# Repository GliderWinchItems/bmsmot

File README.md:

# bmsmot
This board is the control for the BMS (battery monitoring system) for one string of batteries; the contactor function, thermistor inputs for motor coolant, and output drive for enables, relays, and external high current FET sub-boards. A STM32F446RET6 is the main processor on this board.

The contactor function measures the high voltage using a STM32L431RCT6, ground isolated and communicates readings to the main processor via uart with opto-isolator. It also measures battery string current using an external Hall-effect sensor.

The main board provides for the CAN bus cabling to the BMS modules to loop back and apply +12v current to both ends of the CAN cabling, as well as in & out connectors for other nodes on the CAN bus. Provision is for a second CAN bus.

The software provides the EMC (Energy Management Control) and MMC (Motor Management Control) functions for one battery/motor installation.

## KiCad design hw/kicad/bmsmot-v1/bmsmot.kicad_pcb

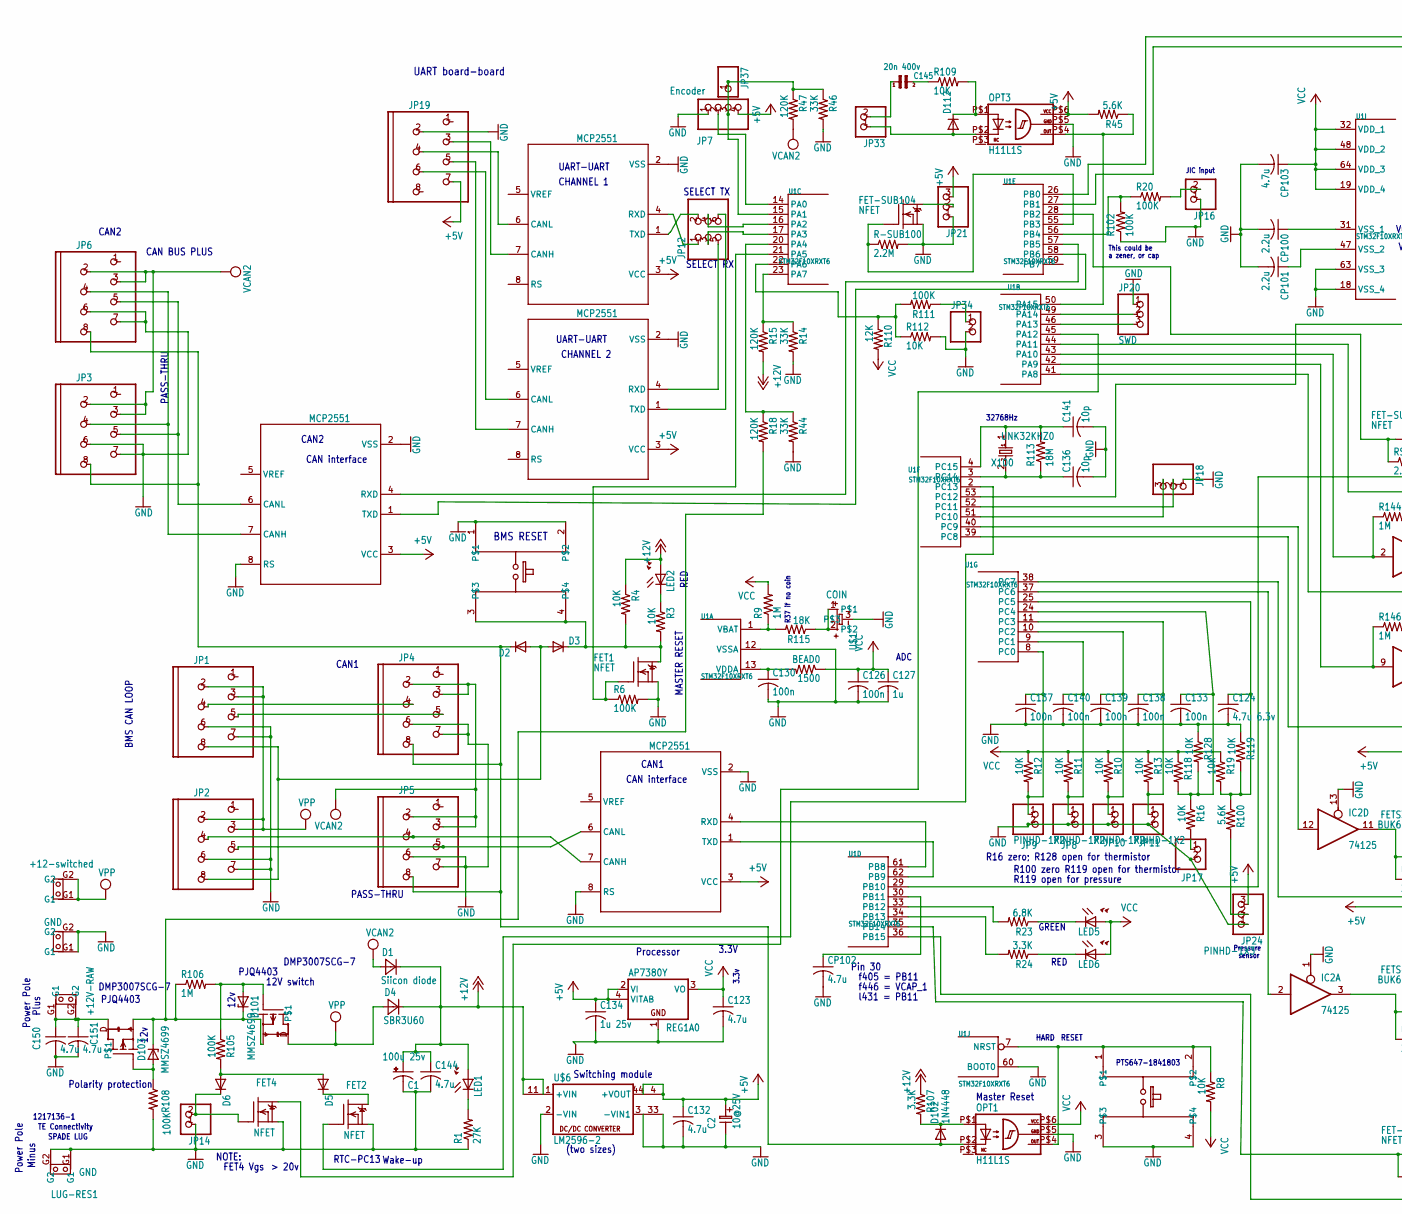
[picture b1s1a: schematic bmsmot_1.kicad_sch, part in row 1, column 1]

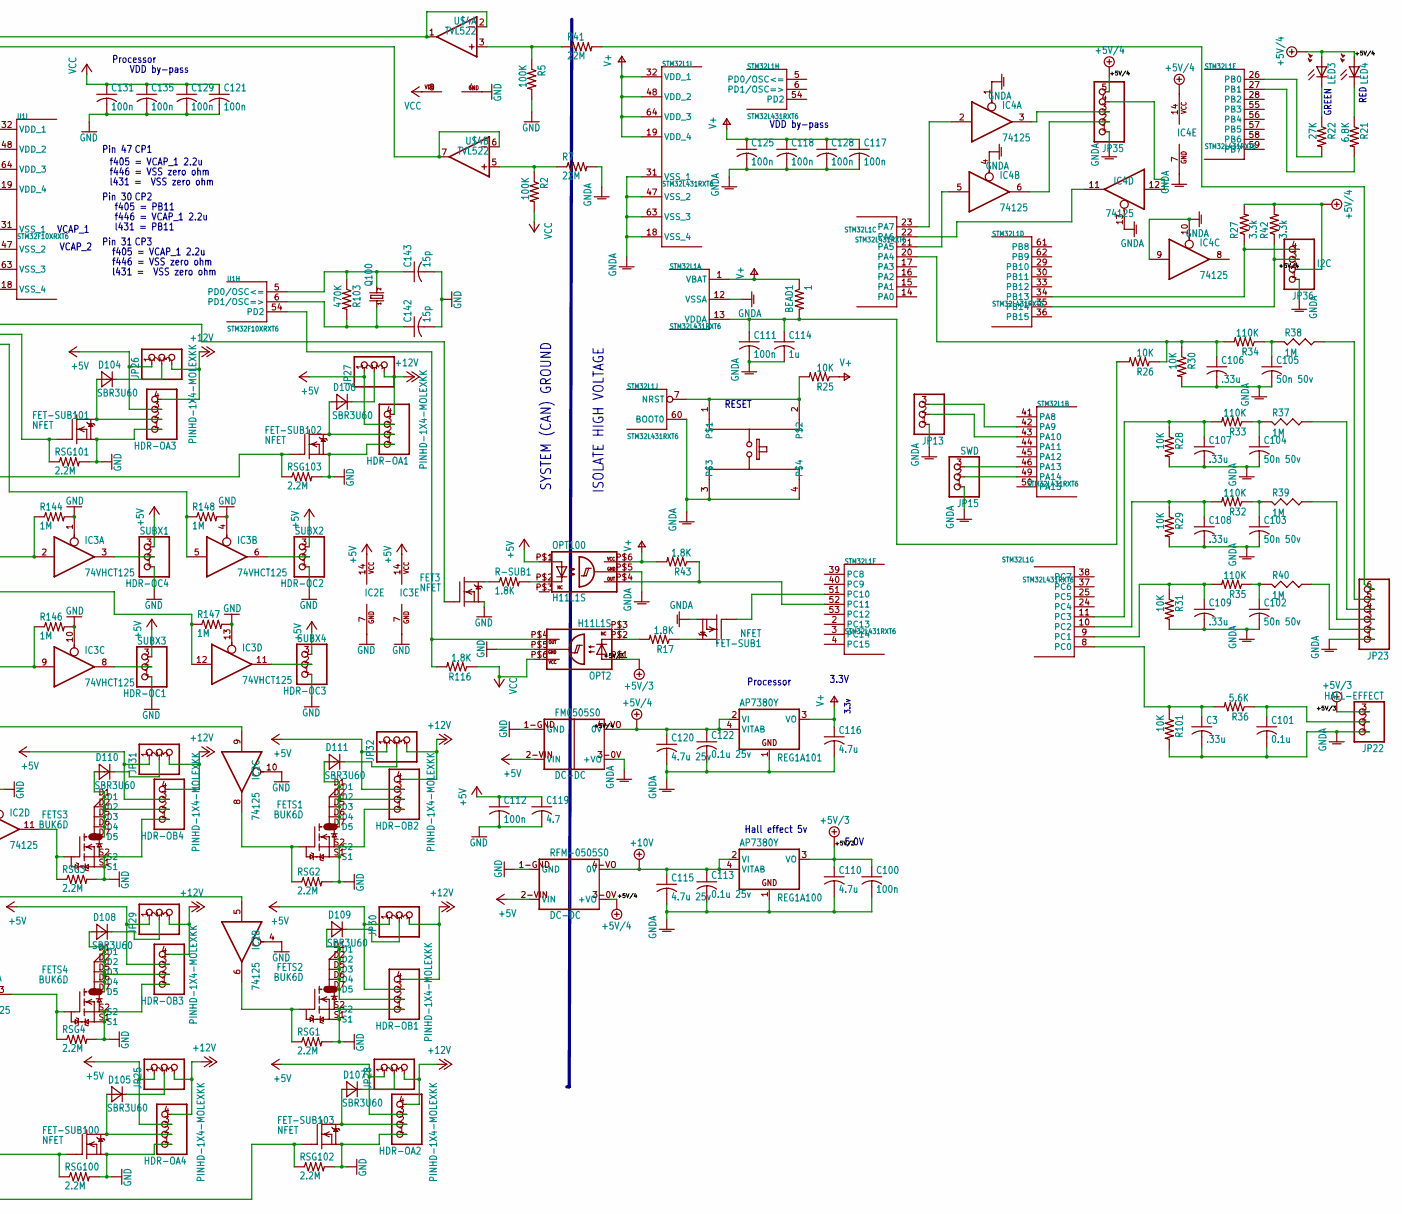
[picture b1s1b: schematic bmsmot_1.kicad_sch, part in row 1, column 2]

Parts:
+12SW0: +12-switched; SPADE_TAB
BEAD0: 1500; R0603
BEAD1: 1; R0603
BMS-RESET0: E-SWITCH2
C1: 100u 25v; E5-8,5
C2: 10@25V; ES-2,5L
C3, C106, C107, C108, C109: .33u; C0603
C100, C111, C112, C117, C118, C121, C125, C126, C128, C129, C130, C131, C133, C135, C137, C138, C139, C140: 100n; C0603
C101: 0.1u; C0603
C102, C103, C104, C105: 50n 50v; C0603
C110, C116, C123, C132: 4.7u; C0603
C113, C122: 0.1u 25v; C0603
C114, C127: 1u; C0603
C115, C120: 4.7u 25v; C0805
C119: 4.7; C0805
C124: 4.7u 6.3v; C0603
C134: 1u 25v; C0603
C136, C141: 10p; C0603
C142, C143: 15p; C0603
C144, C150, C151: 4.7u; C0805
C145: 20n 400v; 1210
CP100, CP101: 2.2u; C0603
CP102, CP103: 4.7u; C0603
D1: Siicon diode; POWERDI123
D2, D3, D5, D6, D112: DIODE-SOD323-R; SOD323-R
D4, D104, D105, D106, D107, D108, D109, D110, D111: SBR3U60; POWERDI123
D101, D103: MMSZ4699; SOD80C
D102: 1N4448; SOD123
FET1, FET2, FET3, FET4: NFET; SOT-23
FET-SUB1, FET-SUB100, FET-SUB101, FET-SUB102, FET-SUB103, FET-SUB104: NFET; SOT-23
FETS1, FETS2, FETS3, FETS4: BUK6D; DFN2020-6
FM0505S0: DC-DC
GND0: GND; SPADE_TAB
HDR-OA1, HDR-OA2, HDR-OA3, HDR-OA4: PINHD-1X4-MOLEXKK; 1X4-MOLEXKK
HDR-OB1, HDR-OB2, HDR-OB3, HDR-OB4: PINHD-1X4-MOLEXKK; 1X4-MOLEXKK
HDR-OC1: SUBX3; 1X03
HDR-OC2: SUBX2; 1X03
HDR-OC3: SUBX4; 1X03
HDR-OC4: SUBX1; 1X03
IC1, IC100, IC101, IC102: MCP2551; SO-08
IC2, IC4: 74125; TSSOP14
IC3: 74VHCT125; TSSOP14
JP1, JP2, JP3, JP4, JP5, JP6, JP19: MOD8P8C
JP7: Encoder; 1X04
JP8, JP9, JP10, JP11, JP14, JP16, JP17, JP33, JP34: PINHD-1X2; 1X02
JP12: PINHD-2X3; 2X03
JP13, JP18, JP21, JP24, JP25, JP26, JP27, JP28, JP29, JP30, JP31, JP32: PINHD-1X3; 1X03
JP15, JP20: SWD; 1X03
JP22: HALL-EFFECT; 1X03
JP23: PINHD-1X6; 1X06
JP35: PINHD-1X5; 1X05
JP36: I2C; 1X04
JP37: PINHD-1X1; 1X01
LED1, LED2, LED3, LED4, LED5, LED6: LEDCHIP-LED0603; CHIP-LED0603
LUG-GND1: +12V-RAW; SPADE_TAB
LUG-RES1: GND; SPADE_TAB
OPT1, OPT2, OPT3, OPT100: H11L1S; SMD-6
Q100: CRYTALHC49S; HC49_S
R1, R22: 27K; R0603
R2, R5, R6, R20, R102, R105, R108, R111: 100K; R0603
R3, R4, R8, R10, R11, R12, R13, R16, R19, R25, R26, R28, R29, R30, R31, R101, R109, R112, R118, R119, R128: 10K; R0603
R7, R41: 22M; 0207_5V
R9, R106: 1M; R0603
R14, R44, R46: 33K; R0603
R15, R18, R47: 120K; R0603
R17, R43, R116: 1.8K; R0603
R21, R23: 6.8K; R0603
R24, R107: 3.3K; R0603
R27, R42: 3.3k; R0603
R32, R33, R34, R35: 110K; R0603
R36, R45, R100: 5.6K; R0603
R37, R38, R39, R40: 1M; RS-2,5
R103: 470K; R0603
R110: 12K; R0603
R113: 18M; R0603
R115: 18K; R0603
R144, R146, R147, R148: 1M; R0402
R-SUB1: 1.8K; R0603
R-SUB100: 2.2M; R0603
REG1A0, REG1A100, REG1A101: AP7380Y; SOT89
RESET0, RESET1: E-SWITCH2
RFM-0505S0: DC-DC
RSG1, RSG2, RSG3, RSG4, RSG100, RSG101, RSG102, RSG103: 2.2M; R0603
STM32L1: STM32L431RXT6; TQFP64
U1: STM32F10XRXT6; TQFP64
U$1: COIN
U$2, U$3: PJQ4403P; DFN3333-8L
U$4: TVL522; VSSOP8
U$6: LM2596-2; LM2569SW2
UNK32KHZ0: X100; 32KHZ

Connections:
+5V: C2.1, C112.1, C119.1, C132.1, C134.1, FM0505S0.2-VIN (VIN), HDR-OA1.3, HDR-OA2.3, HDR-OA3.3, HDR-OA4.3, HDR-OB1.3, HDR-OB2.3, HDR-OB3.3, HDR-OB4.3, HDR-OC1.3, HDR-OC2.3, HDR-OC3.3, HDR-OC4.3, IC1.3 (VCC), IC2.14 (VCC), IC3.14 (VCC), IC100.3 (VCC), IC101.3 (VCC), IC102.3 (VCC), JP7.4, JP19.7 (4), JP21.3, JP24.3, JP25.1, JP26.1, JP27.1, JP28.1, JP29.1, JP30.1, JP31.1, JP32.1, OPT3.P$6 (VCC), OPT100.P$1 (A), R45.2, REG1A0.2 (VI), REG1A0.4 (VITAB), RFM-0505S0.2-VIN (VIN), U$6.4 (+VOUT1), U$6.44 (+VOUT)
+5V/3: C100.1, C110.1, JP22.3, OPT2.P$1 (A), REG1A100.3 (VO)
+5V/4: C120.1, C122.1, FM0505S0.4-VO (0V), IC4.14 (VCC), JP35.5, JP36.2, LED3.A, LED4.A, R27.2, R42.2, REG1A101.2 (VI), REG1A101.4 (VITAB), RFM-0505S0.3-0V (+VO)
+10V: C113.1, C115.1, REG1A100.2 (VI), REG1A100.4 (VITAB), RFM-0505S0.4-VO (0V)
+12V: C1.+, C144.1, D1.C, D4.C, HDR-OA1.4, HDR-OA2.4, HDR-OA3.4, HDR-OA4.4, HDR-OB1.4, HDR-OB2.4, HDR-OB3.4, HDR-OB4.4, JP25.3, JP26.3, JP27.3, JP28.3, JP29.3, JP30.3, JP31.3, JP32.3, LED1.A, LED2.A, R4.1, R15.2, R107.1, U$6.1 (+VIN), U$6.11 (+VIN1)
+12V-POLARITY: D101.C, D103.C, R18.2, R106.1, U$2.S (S3), U$3.S (S3)
+12V-RAW: C150.1, C151.1, LUG-GND1.G1, LUG-GND1.G2, U$2.D
AC-12VRMS: JP34.1, R111.1
AC-OPTO-1: D112.A, JP33.1, OPT3.P$2 (C)
AC-OPTO-2: C145.1, JP33.2
AC-OPTO-IN: D112.C, OPT3.P$1 (A), R109.2
AC-OPTO-RC: C145.2, R109.1
BUFF1-PC8: IC2.9 (I), U1.39 (PC8)
BUFF2-PC7: IC2.5 (I), U1.38 (PC7)
BUFF5-PC9: IC2.12 (I), U1.40 (PC9)
BUFF6-PC6: IC2.2 (I), U1.37 (PC6)
CANH1: IC102.7 (CANH), JP2.4 (6), JP5.4 (6)
CANH1-FT: JP1.4 (6), JP4.4 (6)
CANH2: IC1.7 (CANH), JP3.4 (6), JP6.4 (6)
CANL1: IC102.6 (CANL), JP2.5 (3), JP5.5 (3)
CANL1-FT: JP1.5 (3), JP4.5 (3)
CANL2: IC1.6 (CANL), JP3.5 (3), JP6.5 (3)
CHAN1-RX: IC100.4 (RXD), JP12.1
CHAN1-TX: IC100.1 (TXD), JP12.2
CHAN1_CAN-L: IC100.6 (CANL), JP19.4 (6)
CHAN2-RX: IC101.4 (RXD), JP12.5
CHAN2-TX: IC101.1 (TXD), JP12.6
CHAN2_CAN-H: IC101.7 (CANH), JP19.5 (3)
CHAN2_CAN-L: IC101.6 (CANL), JP19.6 (7)
CHAN-1_CAN-H: IC100.7 (CANH), JP19.3 (2)
COIN+: R115.1, U$1.1, U$1.2
DRAIN-SUB1: D111.A, FETS1.D1, FETS1.D2, FETS1.D5 (D3), FETS1.D6 (D4), FETS1.D7 (D5), HDR-OB2.2
DRAIN-SUB2: D109.A, FETS2.D1, FETS2.D2, FETS2.D5 (D3), FETS2.D6 (D4), FETS2.D7 (D5), HDR-OB1.2
DRAIN-SUB5: D110.A, FETS3.D1, FETS3.D2, FETS3.D5 (D3), FETS3.D6 (D4), FETS3.D7 (D5), HDR-OB4.2
DRAIN-SUB6: D108.A, FETS4.D1, FETS4.D2, FETS4.D5 (D3), FETS4.D6 (D4), FETS4.D7 (D5), HDR-OB3.2
DRAIN-SUB13: D107.A, FET-SUB103.3 (D), HDR-OA2.2
DRAIN-SUB14: D106.A, FET-SUB102.3 (D), HDR-OA1.2
DRAIN-SUB17: D104.A, FET-SUB101.3 (D), HDR-OA3.2
DRAIN-SUB18: D105.A, FET-SUB100.3 (D), HDR-OA4.2
DSEL-OA1: D106.C, JP27.2
DSEL-OA2: D107.C, JP28.2
DSEL-OA3: D104.C, JP26.2
DSEL-OA4: D105.C, JP25.2
DSEL-OB1: D109.C, JP30.2
DSEL-OB2: D111.C, JP32.2
DSEL-OB3: D108.C, JP29.2
DSEL-OB4: D110.C, JP31.2
FET1-DRAIN-MASTER-RESET: BMS-RESET0.3, BMS-RESET0.4, D3.C, FET1.3 (D), R3.2, R4.2
FET2-DRAIN: D5.C, FET2.3 (D)
FET3-DRAIN-UART5-TX: FET3.3 (D), R-SUB1.1
FET103-GATE: D103.A, R108.1, U$2.G
FET-SUB9-DRAIN: FET-SUB104.3 (D), JP21.2
GATE-SUB4-PB10: FET-SUB102.1 (G), RSG103.1, U1.29 (PB10)
GATE-SUB7-PB2: FET-SUB101.1 (G), RSG101.1, U1.28 (PB2)
GATE-SUBH3-PB15: FET-SUB103.1 (G), RSG102.1, U1.36 (PB15)
GATE-SUBH8-PB14: FET-SUB100.1 (G), RSG100.1, U1.35 (PB14)
GND: BMS-RESET0.1, BMS-RESET0.2, C1.-, C2.2, C112.2, C119.2, C121.2, C123.2, C124.2, C126.2, C127.2, C129.2, C130.2, C131.2, C132.2, C133.2, C134.2, C135.2, C136.2, C137.2, C138.2, C139.2, C140.2, C141.2, C142.2, C143.2, C144.2, C150.2, C151.2, CP100.2, CP101.2, CP102.2, CP103.2, FET1.2 (S), FET2.2 (S), FET3.2 (S), FET4.2 (S), FET-SUB100.2 (S), FET-SUB101.2 (S), FET-SUB102.2 (S), FET-SUB103.2 (S), FET-SUB104.2 (S), FETS1.S1, FETS1.S2, FETS2.S1, FETS2.S2, FETS3.S1, FETS3.S2, FETS4.S1, FETS4.S2, FM0505S0.1-GND (GND), GND0.G1, GND0.G2, HDR-OA1.1, HDR-OA2.1, HDR-OA3.1, HDR-OA4.1, HDR-OB1.1, HDR-OB2.1, HDR-OB3.1, HDR-OB4.1, HDR-OC1.1, HDR-OC2.1, HDR-OC3.1, HDR-OC4.1, IC1.2 (VSS), IC1.8 (RS), IC2.1 (OE), IC2.4 (OE), IC2.7 (GND), IC2.10 (OE), IC2.13 (OE), IC3.1 (OE), IC3.4 (OE), IC3.7 (GND), IC3.10 (OE), IC3.13 (OE), IC100.2 (VSS), IC101.2 (VSS), IC102.2 (VSS), IC102.8 (RS), JP1.6 (7), JP1.7 (4), JP2.6 (7), JP2.7 (4), JP3.6 (7), JP3.7 (4), JP4.6 (7), JP4.7 (4), JP5.6 (7), JP5.7 (4), JP6.6 (7), JP6.7 (4), JP7.1, JP8.2, JP9.2, JP10.2, JP11.2, JP14.1, JP16.1, JP17.2, JP18.1, JP19.2 (5), JP20.1, JP21.1, JP24.1, JP34.2, LUG-RES1.G1, LUG-RES1.G2, OPT1.P$5 (GND), OPT2.P$5 (GND), OPT3.P$5 (GND), R1.1, R5.2, R6.2, R14.2, R44.2, R46.2, R102.1, R108.2, R112.2, R119.1, R128.1, R144.2, R146.2, R147.2, R148.2, R-SUB100.2, REG1A0.1 (GND), RESET0.3, RESET0.4, RFM-0505S0.1-GND (GND), RSG1.2, RSG2.2, RSG3.2, RSG4.2, RSG100.2, RSG101.2, RSG102.2, RSG103.2, U1.12 (VSSA), U1.18 (VSS_4), U1.60 (BOOT0), U1.63 (VSS_3), U$1.3, U$4.4 (GND), U$6.2 (-VIN), U$6.3 (-VIN1), U$6.33 (-VIN2)
GNDA: C3.2, C100.2, C101.2, C102.2, C103.2, C104.2, C105.2, C106.2, C107.2, C108.2, C109.2, C110.2, C111.2, C113.2, C114.2, C115.2, C116.2, C117.2, C118.2, C120.2, C122.2, C125.2, C128.2, FET-SUB1.2 (S), FM0505S0.3-0V (+VO), IC4.1 (OE), IC4.4 (OE), IC4.7 (GND), IC4.9 (I), IC4.10 (OE), IC4.13 (OE), JP13.1, JP15.1, JP22.1, JP23.1, JP35.1, JP36.1, OPT100.P$5 (GND), R7.2, R28.2, R29.2, R30.2, R31.2, R101.2, REG1A100.1 (GND), REG1A101.1 (GND), RESET1.3, RESET1.4, STM32L1.12 (VSSA), STM32L1.18 (VSS_4), STM32L1.31 (VSS_1), STM32L1.47 (VSS_2), STM32L1.60 (BOOT0), STM32L1.63 (VSS_3)
HDRXA1: HDR-OC1.2, IC3.8 (O)
HDRXA2: HDR-OC2.2, IC3.6 (O)
HDRXA3: HDR-OC3.2, IC3.11 (O)
HDRXA4: HDR-OC4.2, IC3.3 (O)
HV1: JP23.4, R37.1
HV1-1: C104.1, R33.1, R37.2
HV1-2: C103.1, R32.1, R39.2
HV1-3: C102.1, R35.1, R40.2
HV1-4: C105.1, R34.1, R38.2
HV2: JP23.3, R39.1
HV3: JP23.2, R40.1
HV-AC: JP23.5, R38.1
HV-HALL-SIGNAL: C101.1, JP22.2, R36.1
HV-PLUS: JP23.6, R41.2
HV_LEAK-: R2.1, R7.1, U$4.5 (+IN)
HV_LEAK_DIV+: R5.1, R41.1, U$4.3 (+IN)
JIC-INPUT: JP16.2, R20.2
JP17-PC4: JP17.1, R16.2
JP24-PC5: JP24.2, R100.2
L431-LED-GRN-CATHODE: LED3.C, R22.1
L431-LED-RED-CATHODE: LED4.C, R21.1
L431-PA13-SWDIO: JP15.3, STM32L1.46 (PA13)
L431-PA14-SWCLK: JP15.2, STM32L1.49 (PA14)
L431-PB0-LED-GRN: R22.2, STM32L1.26 (PB0)
L431-PB1-LED-RED: R21.2, STM32L1.27 (PB1)
L431-PC10-USART3-TX2: FET-SUB1.1 (G), STM32L1.51 (PC10)
L431-PC11-USART3-RX: OPT100.P$4 (OUT), R43.1, STM32L1.52 (PC11)
L431-UART-TX-FET: FET-SUB1.3 (D), R17.1
L431-USART-TX-OPTO: OPT2.P$2 (C), R17.2
L431-VDDA: BEAD1.2, C111.1, C114.1, R26.2, STM32L1.13 (VDDA)
L-I2C2-SDA: JP36.4, R27.1, STM32L1.34 (PB13)
L-PA5-SPI1-SCK: IC4.5 (I), STM32L1.21 (PA5)
L-PA6-SPI1-MISO: IC4.11 (O), STM32L1.22 (PA6)
L-PA7-SPI1-MOSI: IC4.2 (I), STM32L1.23 (PA7)
L-PB14-I2C2-SDA: JP36.3, R42.1, STM32L1.35 (PB14)
L-SPI1-MISO: IC4.12 (I), JP35.4
L-SPI1-MOSI: IC4.3 (O), JP35.3
L-SPI1-SCK: IC4.6 (O), JP35.2
LED-EXT-GRN-CATHODE: LED5.C, R23.1
LED-EXT-RED-CATHODE: LED6.C, R24.1
LED-EXT-RED-CATHODE2: LED2.C, R3.1
LED_BUS_PWR: LED1.C, R1.2
MASTER-RESET-RESISTOR: D102.C, OPT1.P$1 (A), R107.2
MASTER-RESET-SYS: D2.C, D102.A, JP3.8, JP4.8, JP5.8, JP6.8, OPT1.P$2 (C)
MASTER_RESET1: D2.A, D3.A, JP1.8, JP2.8
unnamed: D6.C, FET4.1 (G), JP14.2
NRST: OPT1.P$4 (OUT), R8.1, RESET0.1, RESET0.2, U1.7 (NRST)
NRST1: R25.2, RESET1.1, RESET1.2, STM32L1.7 (NRST)
PA0-T2C1: JP7.2, U1.14 (PA0)
PA1-T2C2|SYS12V: JP7.3, JP37.1, R46.1, R47.1, U1.15 (PA1)
PA2-USART2-TX: JP12.4, U1.16 (PA2)
PA3-USART2-RX: JP12.3, U1.17 (PA3)
PA4-RSP12V_POLARITY: R18.1, R44.1, U1.20 (PA4)
PA5-MASTER-RESET: FET1.1 (G), R6.1, U1.21 (PA5)
PA6: R110.1, R111.2, R112.1, U1.22 (PA6)
PA7-12V-PROTECT-DIVIDER: R14.1, R15.1, U1.23 (PA7)
PA8-HDRX3: IC3.12 (I), R147.1, U1.41 (PA8)
PA9-HDRX1: IC3.9 (I), R146.1, U1.42 (PA9)
PA9-USART1-TX: JP13.3, STM32L1.42 (PA9)
PA10-HDRX4: IC3.2 (I), R144.1, U1.43 (PA10)
PA10-USART1-RX: JP13.2, STM32L1.43 (PA10)
PA11-HDRX2: IC3.5 (I), R148.1, U1.44 (PA11)
PA12-KEYSW-SENSE: FET4.3 (D), U1.45 (PA12)
PA13-SWDIO: JP20.3, U1.46 (PA13)
PA14-SWCLK: JP20.2, U1.49 (PA14)
PA15-OPTO-OUT: OPT3.P$4 (OUT), R45.1, U1.50 (PA15)
PB0_HVLEAK+: U1.26 (PB0), U$4.1 (OUT), U$4.2 (-IN)
PB1-HV_LEAK-: U1.27 (PB1), U$4.6 (-IN), U$4.7 (OUT)
PB3-SUB9: FET-SUB104.1 (G), R-SUB100.1, U1.55 (PB3)
PB4: R20.1, R102.2, U1.56 (PB4)
PB5-CAN2-RX: IC1.4 (RXD), U1.57 (PB5)
PB6-CAN2-TX: IC1.1 (TXD), U1.58 (PB6)
PB8-CAN1-RX: IC102.4 (RXD), U1.61 (PB8)
PB9-CAN1-TX: IC102.1 (TXD), U1.62 (PB9)
PB11-I2C2-SDA|VCAP1: CP102.1, U1.30 (PB11)
PB12-LED2-GREEN: R23.2, U1.33 (PB12)
PB13-LED3-RED: R24.2, U1.34 (PB13)
PC0-ADC1_IN1: C3.1, R36.2, R101.1, STM32L1.8 (PC0)
PC0-IN10: C137.1, JP9.1, R12.2, U1.8 (PC0)
PC1-ADC1_IN2: C109.1, R31.1, R35.2, STM32L1.9 (PC1)
PC1-IN11: C140.1, JP8.1, R11.2, U1.9 (PC1)
PC2-ADC1-IN3: C108.1, R29.1, R32.2, STM32L1.10 (PC2)
PC2-IN12: C139.1, JP10.1, R10.2, U1.10 (PC2)
PC3-ADC1-IN4: C107.1, R28.1, R33.2, STM32L1.11 (PC3)
PC3-IN13: C138.1, JP11.1, R13.2, U1.11 (PC3)
PC4-ADC1_IN9: C106.1, R26.1, R30.1, R34.2, STM32L1.20 (PA4)
PC4-IN14: C133.1, R16.1, R118.2, R128.2, U1.24 (PC4)
PC5-IN15: C124.1, R19.2, R100.1, R119.2, U1.25 (PC5)
PC10-USART3-TX: JP18.3, U1.51 (PC10)
PC11-USART3-RX: JP18.2, U1.52 (PC11)
PC12-UART5-TX: FET3.1 (G), U1.53 (PC12)
PC13-NFET-GATE: FET2.1 (G), U1.2 (PC13)
PC14_OSC32IN|XTAL: C136.1, R113.1, U1.3 (PC14), UNK32KHZ0.2
PC15-32OSC-OUT: C141.1, R113.2, U1.4 (PC15), UNK32KHZ0.1
PD0_OSC_IN_XTAL: C143.1, Q100.2, R103.1, U1.5 (PD0/OSC<=)
PD1_OSC_OUT: C142.1, Q100.1, R103.2, U1.6 (PD1/OSC=>)
PD2-UART5-RX: OPT2.P$4 (OUT), R116.2, U1.54 (PD2)
PFET-SWITCH-GATE: D101.A, R105.1, R106.2, U$3.G
PFET-SWITCH-OR: D5.A, D6.A, R105.2
SUBH1-FET-GATE: FETS1.G, IC2.8 (O), RSG2.1
SUBH2-FET-GATE: FETS2.G, IC2.6 (O), RSG1.1
SUBH5-FET-GATE: FETS3.G, IC2.11 (O), RSG3.1
SUBH6-FET-GATE: FETS4.G, IC2.3 (O), RSG4.1
UART5-TX: OPT100.P$2 (C), R-SUB1.2
V+: BEAD1.1, C116.1, C117.1, C118.1, C125.1, C128.1, OPT100.P$6 (VCC), R25.1, R43.2, REG1A101.3 (VO), STM32L1.1 (VBAT), STM32L1.19 (VDD_4), STM32L1.32 (VDD_1), STM32L1.48 (VDD_2), STM32L1.64 (VDD_3)
VBAT: R9.1, R115.2, U1.1 (VBAT)
VCAN2: D1.A, JP3.2 (5), JP3.3 (2), JP4.2 (5), JP4.3 (2), JP5.2 (5), JP5.3 (2), JP6.2 (5), JP6.3 (2), R47.2
VCC: BEAD0.1, C121.1, C123.1, C126.1, C127.1, C129.1, C131.1, C135.1, CP103.1, LED5.A, LED6.A, OPT1.P$6 (VCC), OPT2.P$6 (VCC), R2.2, R8.2, R9.2, R10.1, R11.1, R12.1, R13.1, R19.1, R110.2, R116.1, R118.1, REG1A0.3 (VO), U1.19 (VDD_4), U1.32 (VDD_1), U1.48 (VDD_2), U1.64 (VDD_3), U$4.8 (VDD)
VDDA1: BEAD0.2, C130.1, U1.13 (VDDA)
VPP: +12SW0.G1, +12SW0.G2, D4.A, JP1.2 (5), JP1.3 (2), JP2.2 (5), JP2.3 (2), U$3.D
VSS_1-VCAP_1: CP100.1, U1.31 (VSS_1)
VSS_3: CP101.1, U1.47 (VSS_2)

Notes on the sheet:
PJQ4403
VDD by-pass
Minus
This could be
f405 = VCAP_1 2.2u
R37 if no coin
RED
a zener, or cap
DMP3007SCG-7
f446 = VCAP_1 2.2u
PTS647-1841803
Processor
SELECT TX
Master Reset
1217136-1
RESET
l431 = PB11
R100 zero R119 open for thermistor
Pressure
JIC input
5.0V
Power Pole
32768Hz
FET4 Vgs
R16 zero; R128 open for thermistor
TE Connectivity
CAN2
f446 = VSS zero ohm
CHANNEL 1
SYSTEM (CAN) GROUND
CP3
HARD
NOTE:
l431 = VSS zero ohm
CP2
CAN1
Pin 30
VCAP_2
MASTER RESET
R119 open for pressure

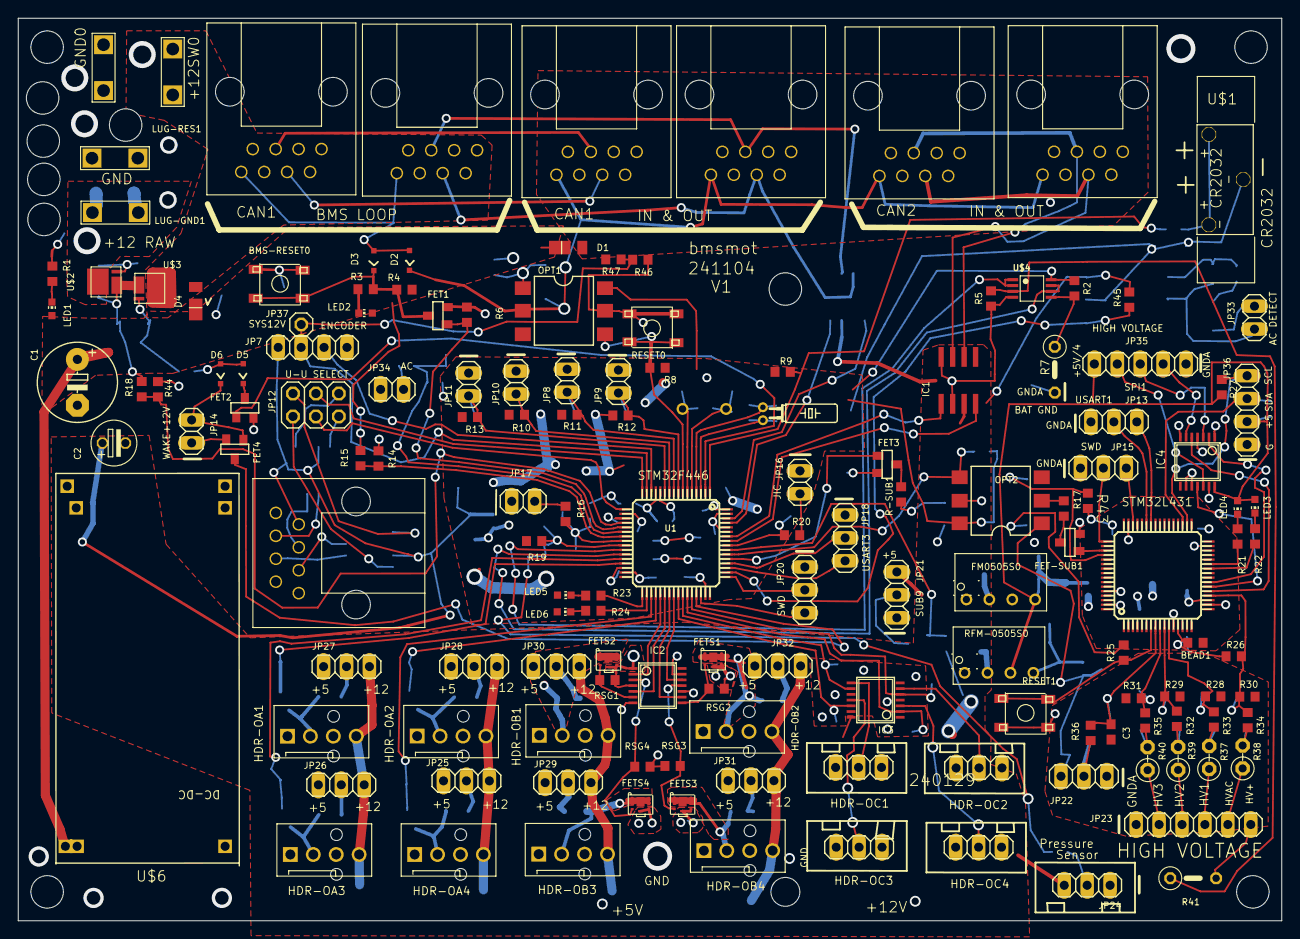
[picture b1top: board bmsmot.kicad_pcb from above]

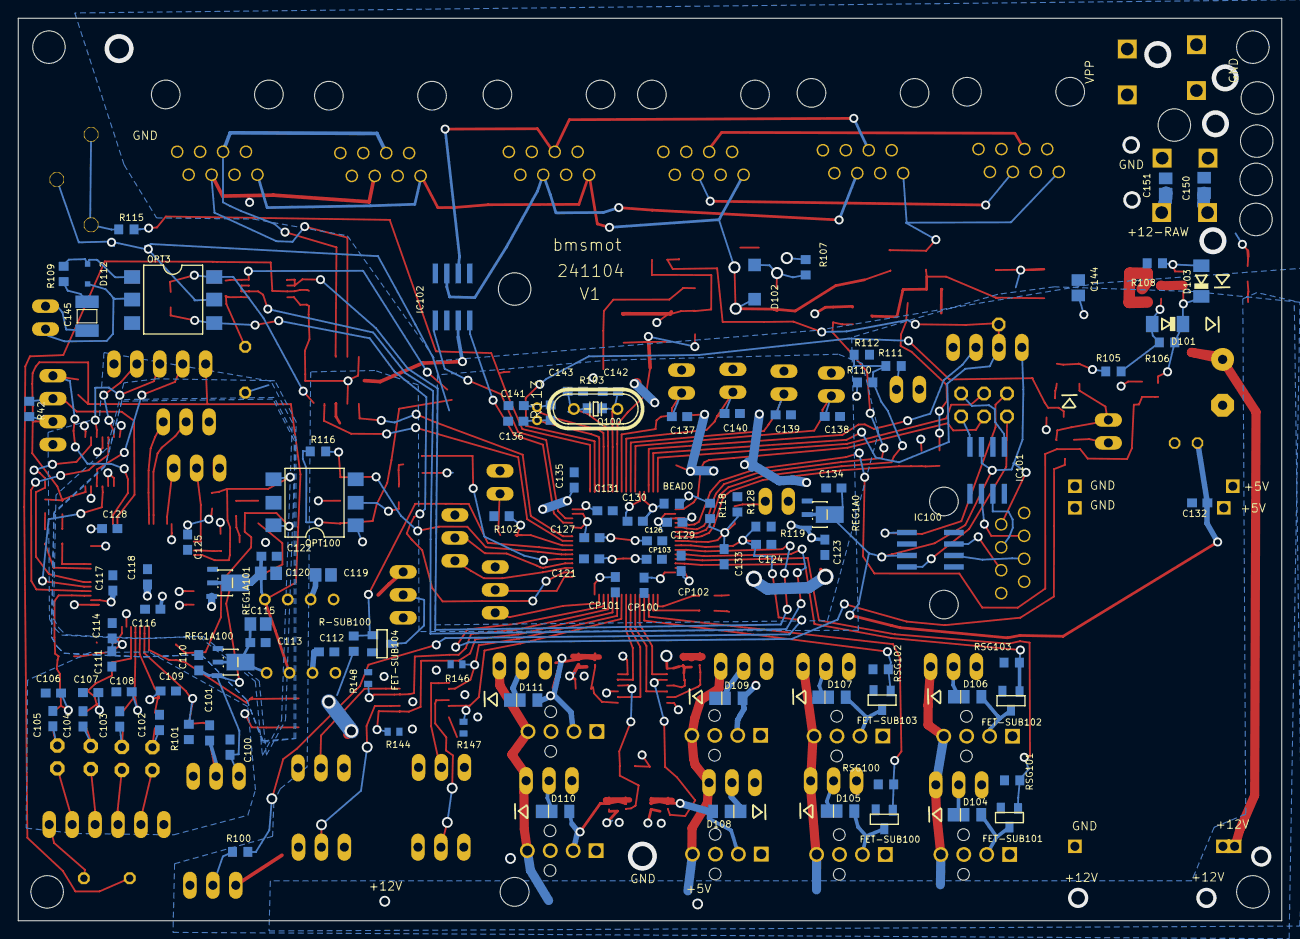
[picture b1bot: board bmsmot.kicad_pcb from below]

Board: 2 copper layers, 140.0 x 100.0 mm, 266 parts (107 on the bottom side), 170 nets.

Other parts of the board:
UNK_HOLE_0: dummyfp0
UNK_HOLE_1: dummyfp1
UNK_HOLE_2: dummyfp2
UNK_HOLE_3: dummyfp3
UNK_HOLE_4: dummyfp4
UNK_HOLE_5: dummyfp5
UNK_HOLE_6: dummyfp6
UNK_HOLE_7: dummyfp7
UNK_HOLE_8: dummyfp8
UNK_HOLE_9: dummyfp9
UNK_HOLE_10: dummyfp10

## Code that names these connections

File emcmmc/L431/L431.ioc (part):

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Mcu.Name=STM32L431R(B-C)Tx
Mcu.Package=LQFP64
Mcu.UserName=STM32L431RCTx
PA0.Signal=GPIO_Output
PA1.Signal=GPIO_Output
PA10.Mode=Asynchronous
PA10.Signal=USART1_RX
PA11.Signal=GPIO_Output
PA12.Signal=GPIO_Output
PA13\ (JTMS-SWDIO).Mode=Serial_Wire
PA13\ (JTMS-SWDIO).Signal=SYS_JTMS-SWDIO
PA14\ (JTCK-SWCLK).Mode=Serial_Wire
PA14\ (JTCK-SWCLK).Signal=SYS_JTCK-SWCLK
PA2.Signal=GPIO_Output
PA3.Signal=GPIO_Output
PA4.Signal=ADCx_IN9
PA5.Mode=Full_Duplex_Master
PA5.Signal=SPI1_SCK
PA6.Mode=Full_Duplex_Master
PA6.Signal=SPI1_MISO
PA7.Mode=Full_Duplex_Master
PA7.Signal=SPI1_MOSI
PA8.Signal=GPIO_Output
PA9.Mode=Asynchronous
PA9.Signal=USART1_TX
PB0.GPIOParameters=PinState,GPIO_Label,GPIO_ModeDefaultOutputPP
PB0.GPIO_Label=LED-GRN
PB0.GPIO_ModeDefaultOutputPP=GPIO_MODE_OUTPUT_OD
PB0.PinState=GPIO_PIN_SET
PB0.Signal=GPIO_Output
PB1.GPIOParameters=PinState,GPIO_Label,GPIO_ModeDefaultOutputPP
PB1.GPIO_Label=LED-RED
PB1.GPIO_ModeDefaultOutputPP=GPIO_MODE_OUTPUT_OD
PB1.PinState=GPIO_PIN_SET
PB1.Signal=GPIO_Output
PB10.Signal=GPIO_Output
PB11.Signal=GPIO_Output
PB12.Signal=GPIO_Output
PB13.Signal=GPIO_Output
PB14.Signal=GPIO_Output
PB15.Signal=GPIO_Output
PB2.Signal=GPIO_Output
PB3\ (JTDO-TRACESWO).Signal=GPIO_Output
PB4\ (NJTRST).Signal=GPIO_Output
PB5.Signal=GPIO_Output
PB6.Signal=GPIO_Output
PB7.Signal=GPIO_Output
PB8.Signal=GPIO_Output
PB9.Signal=GPIO_Output
PC0.Signal=ADCx_IN1
PC1.Signal=ADCx_IN2
PC10.Mode=Asynchronous
PC10.Signal=USART3_TX
PC11.Mode=Asynchronous
PC11.Signal=USART3_RX
PC12.Signal=GPIO_Output
PC13.Signal=GPIO_Output
PC14-OSC32_IN\ (PC14).Signal=GPIO_Output
PC15-OSC32_OUT\ (PC15).Signal=GPIO_Output
PC2.Signal=ADCx_IN3
PC3.Signal=ADCx_IN4
PC4.Signal=GPIO_Output
PC5.Signal=GPIO_Output
PC6.Signal=GPIO_Output
PC7.Signal=GPIO_Output
PC8.Signal=GPIO_Output
PC9.Signal=GPIO_Output
PD2.Signal=GPIO_Output
PH0-OSC_IN\ (PH0).Signal=GPIO_Output
PH1-OSC_OUT\ (PH1).Signal=GPIO_Output
PH3-BOOT0.Signal=GPIO_Output
RCC.HSE_VALUE=8000000
RCC.SYSCLKFreq_VALUE=80000000
RCC.SYSCLKSource=RCC_SYSCLKSOURCE_PLLCLK
board=custom

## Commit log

2022-12-22 Add initial files
2023-03-25 save and backup
2023-03-27 save and backup pcb work
2023-03-28 save work. updating 12v controls
2023-03-29 save and back work
2023-03-30 save and backup. Added battery string float detection
2023-03-31 sub-pwrfet update
2023-04-03 Minor additions to pcb and documentation
2023-04-09 update and save
2023-04-10 changed pcb so BMS 12v not switched. Added sense to wake-up header.
2023-04-20 save latest version of eagle layout. Adds 74VHCT125 and DFN2020 fets, plus other changes
2023-04-22 bmsmot pcb part renumbered
2023-04-23 some renaming of headers
2023-04-23 updated LM2596 switcher to two sizes on pcb
2023-04-24 more pcb updates
2023-04-25 change flyback diode arrangement to select one diode with header
2023-04-30 Added offset ADC input for measuring AC via 12v secondary on a transformer for the EMC-MMC configuration
2023-05-01 updates to pcb
2023-05-01 update txt files
2023-05-07 added spi and i2c to L431
2023-05-14 update bmsmot pcb
2023-05-15 update pcb eagle files
2023-05-17 update check
2023-06-26 bmsmot-v1 updates. emcmmc added. F446 and L431 led morse_trap working. Much more to do.
2023-06-26 cleanup L431/build
2023-06-27 yprintf working on both F446 and L431. ADC on L431 sequence running but not tested
2023-10-23 Working out bugs in RYTast
2023-10-24 RyTask debugging in progress.
2023-10-28 relay pull-in test
2023-10-31 adding functions. work on adc
2023-11-14 save and backup work
2023-11-15 added ods files
2023-11-23 fast summing work save
2023-11-26 asm of adc2 processing . save work
2023-11-27 save work
2023-12-03 adc2 cycles parameterized
2023-12-04 add ADC docs
2023-12-05 added filter to offset and main to check that it works
2023-12-09 save work. memory-memory dma experiment with saving ADC2 raw readings to an array.
2023-12-12 save work on adc1 output
2023-12-14 debugging OC1-4
2023-12-15 begin eagle sub-pwr-fet-v2 layout
2023-12-15 clean eagle file
2023-12-19 pwrfet subboard v2 work
2023-12-20 latest tweaks to sub-pwrfet-v2
2023-12-21 added sub-pwrfet-v3 using ADP3120 FET driver. v2 uses GDG0543
2023-12-22 Begin work on CoolingTask
2023-12-23 CoolingTask work save
2023-12-28 pwrfet-v4 added but layout not complete
2023-12-30 add sub-pwrfet-v4, which has gates and comparator for current limiting
2023-12-30 updates to v4 subboard
2024-01-06 pwrfet-v4 update
2024-01-07 save latest tweaks of pcbs
2024-01-18 update pwrfet designs
2024-02-19 lastest with v6 order
2024-02-27 add missing file
2024-03-06 save. debugging cangateBMS C command
2024-03-07 update bmsmot-v1 to add PA4 adc of RSP power input voltage and option on encoder to monitor system12v CAN voltage
2024-03-08 save work. Debugging motor ramping
2024-03-10 save motor ramping work
2024-03-11 motor control may work, but needs further testing
2024-08-12 RTC enable update
2024-08-22 fix script-all
2024-08-31 update work with ldrfixed F446
2024-09-01 changed org to 0x10000 from 0xC000
2024-09-08 emcmmc F446 Begin gateway and stringchrg task work
2024-09-08 moving forward
2024-09-09 save before closing for the night
2024-09-10 separated CAN id table to gateway_table.c/h. inline bsearch for lookup added
2024-09-10 more gateway tables
2024-09-11 changed const table for CAN id lookup to include a CAN id remap to avoid multiple lookups. a
2024-09-12 update work
2024-09-13 added sending CAN msgs to ELCON, but with HV not connected
2024-09-16 added missing BMS timeout
2024-09-29 major revision of struct within struct. Compiles, runs but needs debugging
2024-10-03 save work needs debugging.
2024-10-21 major revisions for ELCON charging. Compiles only
2024-11-04 update eagle files
2024-11-05 update bmsmot eagle files
2025-04-28 added flag and timeout to stop sending ELCON polling msgs when someone else has sent a polling msg, such as cangate
2025-05-10 save string charger work. Discovery phase seems-to-work
2025-05-16 Save Stringchrg function work. Sort of works
2025-09-18 add datasheets
2025-11-10 add kicad directory with conversion from eagle 4 to eagle 6.5 to kicad
